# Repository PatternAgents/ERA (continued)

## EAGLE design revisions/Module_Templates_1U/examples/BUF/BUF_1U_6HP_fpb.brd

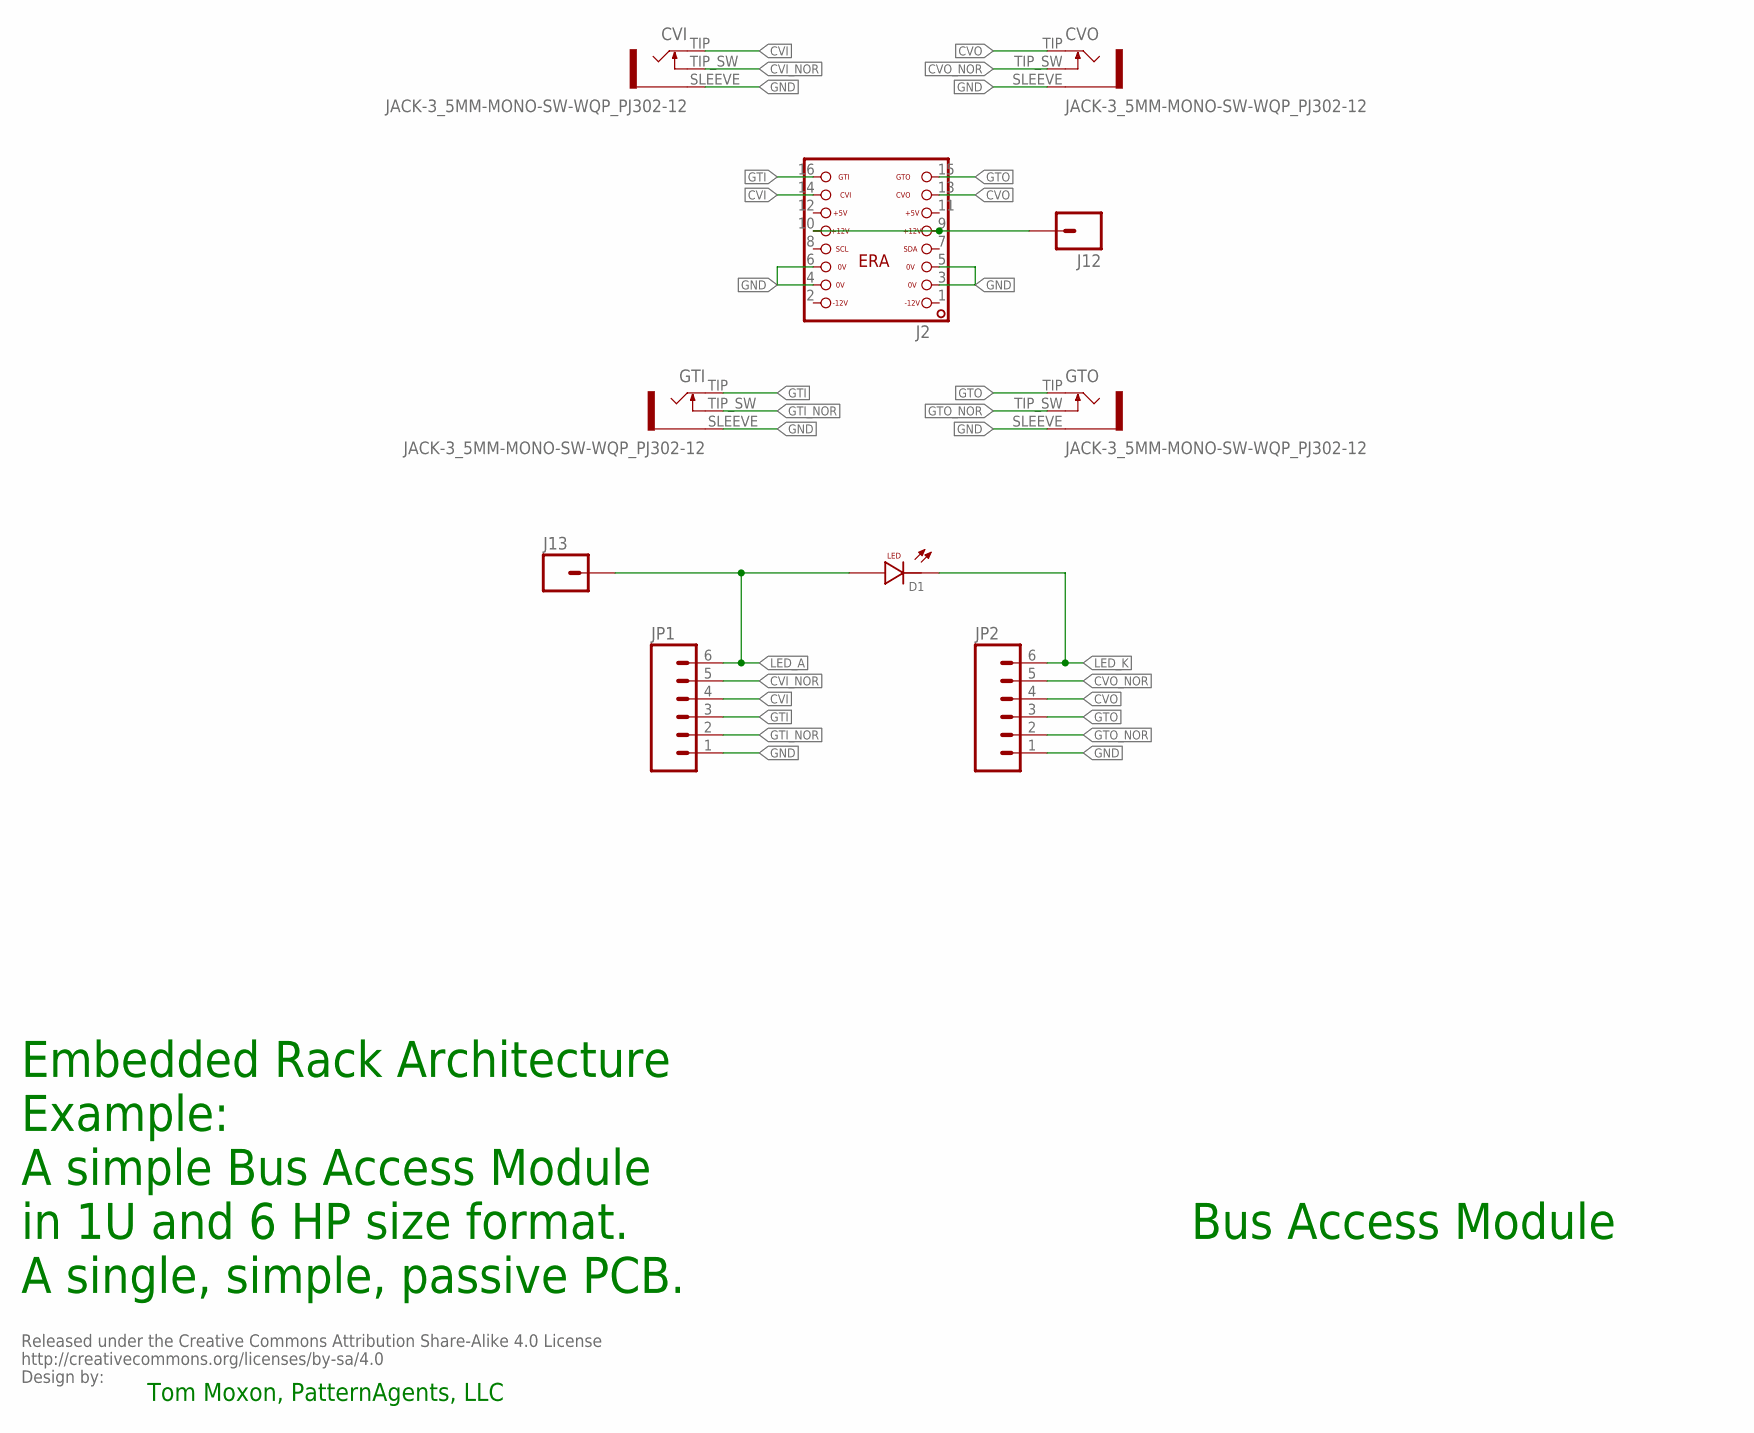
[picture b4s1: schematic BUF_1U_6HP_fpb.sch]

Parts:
CVI: JACK-3_5MM-MONO-SW-WQP_PJ302-12; WQP_PJ301M-12
CVO: JACK-3_5MM-MONO-SW-WQP_PJ302-12; WQP_PJ301M-12
D1: LED; LED3MM
GTI: JACK-3_5MM-MONO-SW-WQP_PJ302-12; WQP_PJ301M-12
GTO: JACK-3_5MM-MONO-SW-WQP_PJ302-12; WQP_PJ301M-12
J2: ERA-NOSILK
J12, J13: M01PTH; 1X01
JP1, JP2: M06SIP; 1X06
TOMMOXON: BY_CC_SA_TEXTNULL; NULL_SYM

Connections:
CVI: CVI.TIP, J2.14, JP1.4
CVI_NOR: CVI.TIP_SW, JP1.5
CVO: CVO.TIP, J2.13, JP2.4
CVO_NOR: CVO.TIP_SW, JP2.5
GND: CVI.SLEEVE, CVO.SLEEVE, GTI.SLEEVE, GTO.SLEEVE, J2.3, J2.4, J2.5, J2.6, JP1.1, JP2.1
GTI: GTI.TIP, J2.16, JP1.3
GTI_NOR: GTI.TIP_SW, JP1.2
GTO: GTO.TIP, J2.15, JP2.3
GTO_NOR: GTO.TIP_SW, JP2.2
LED_A: D1.A (ANODE), J13.1, JP1.6
LED_K: D1.K (CATHODE), JP2.6
unnamed: J2.9, J2.10, J12.1

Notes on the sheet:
Bus Access Module
Embedded Rack Architecture Example: A simple Bus Access Module in 1U and 6 HP size format. A single, simple, passive PCB.
Tom Moxon, PatternAgents, LLC

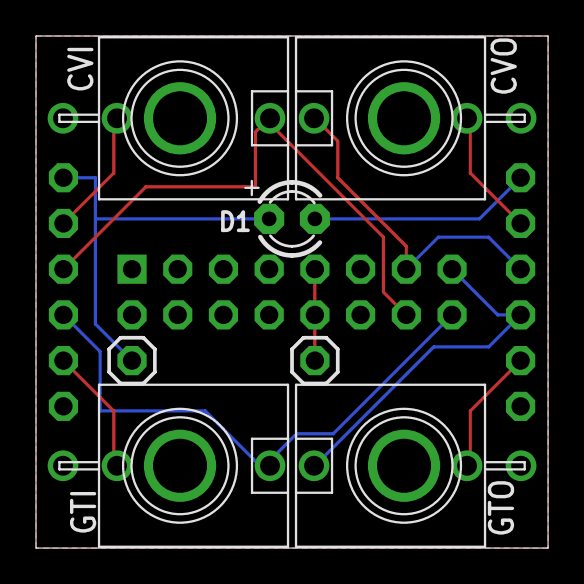
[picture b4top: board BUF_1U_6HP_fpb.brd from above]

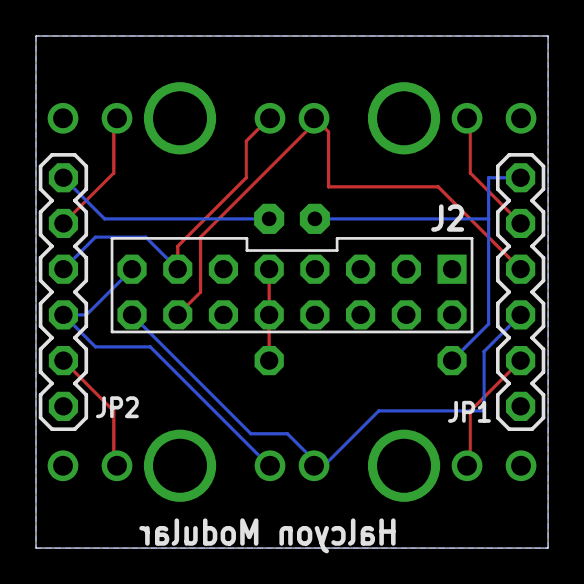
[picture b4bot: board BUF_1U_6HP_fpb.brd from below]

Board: 2 copper layers, 28.4 x 28.4 mm, 11 parts (3 on the bottom side), 12 nets.
